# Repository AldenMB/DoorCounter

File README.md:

# DoorCounter
A IR beam detector for counting when people enter or exit a room, running on a Raspberry Pi Pico.

The DS1302 driver is from [Omar Benhamid](https://github.com/omarbenhamid/micropython-ds1302-rtc). Thanks Omar!

The rotary encoder driver is from [Mike Teachman](https://github.com/miketeachman/micropython-rotary). Thanks Mike!

The circuit board will be held in using 5/16 inch 2-28 pan-head screws. The heads have a diameter of 5/32 inches = 4 mm, The threaded portion has an exterior diameter of 3/32in = 2.3mm, and an inner diameter of about 1/16in = 1.6mm. They measure 3/8 inch in length, counting the head.

## Prototype error
Caution: in my first batch of boards I made an error in the schematic. Of course I take full responsibility, but I feel some blame shoudl also be shared by whoever decided to give one pin of the SD card the designation `DI` and another one the designation `D1`.

The error has already been fixed on the schematic, and it's easy enough to fix. Just break the trace going from `GP3` to the SD card, and instead run a wire to one side of `R3`. Like this:

Of course, if you don't use the SD card then this makes no difference. It is still pulled up to the `3V3` line with a 10k resistor.

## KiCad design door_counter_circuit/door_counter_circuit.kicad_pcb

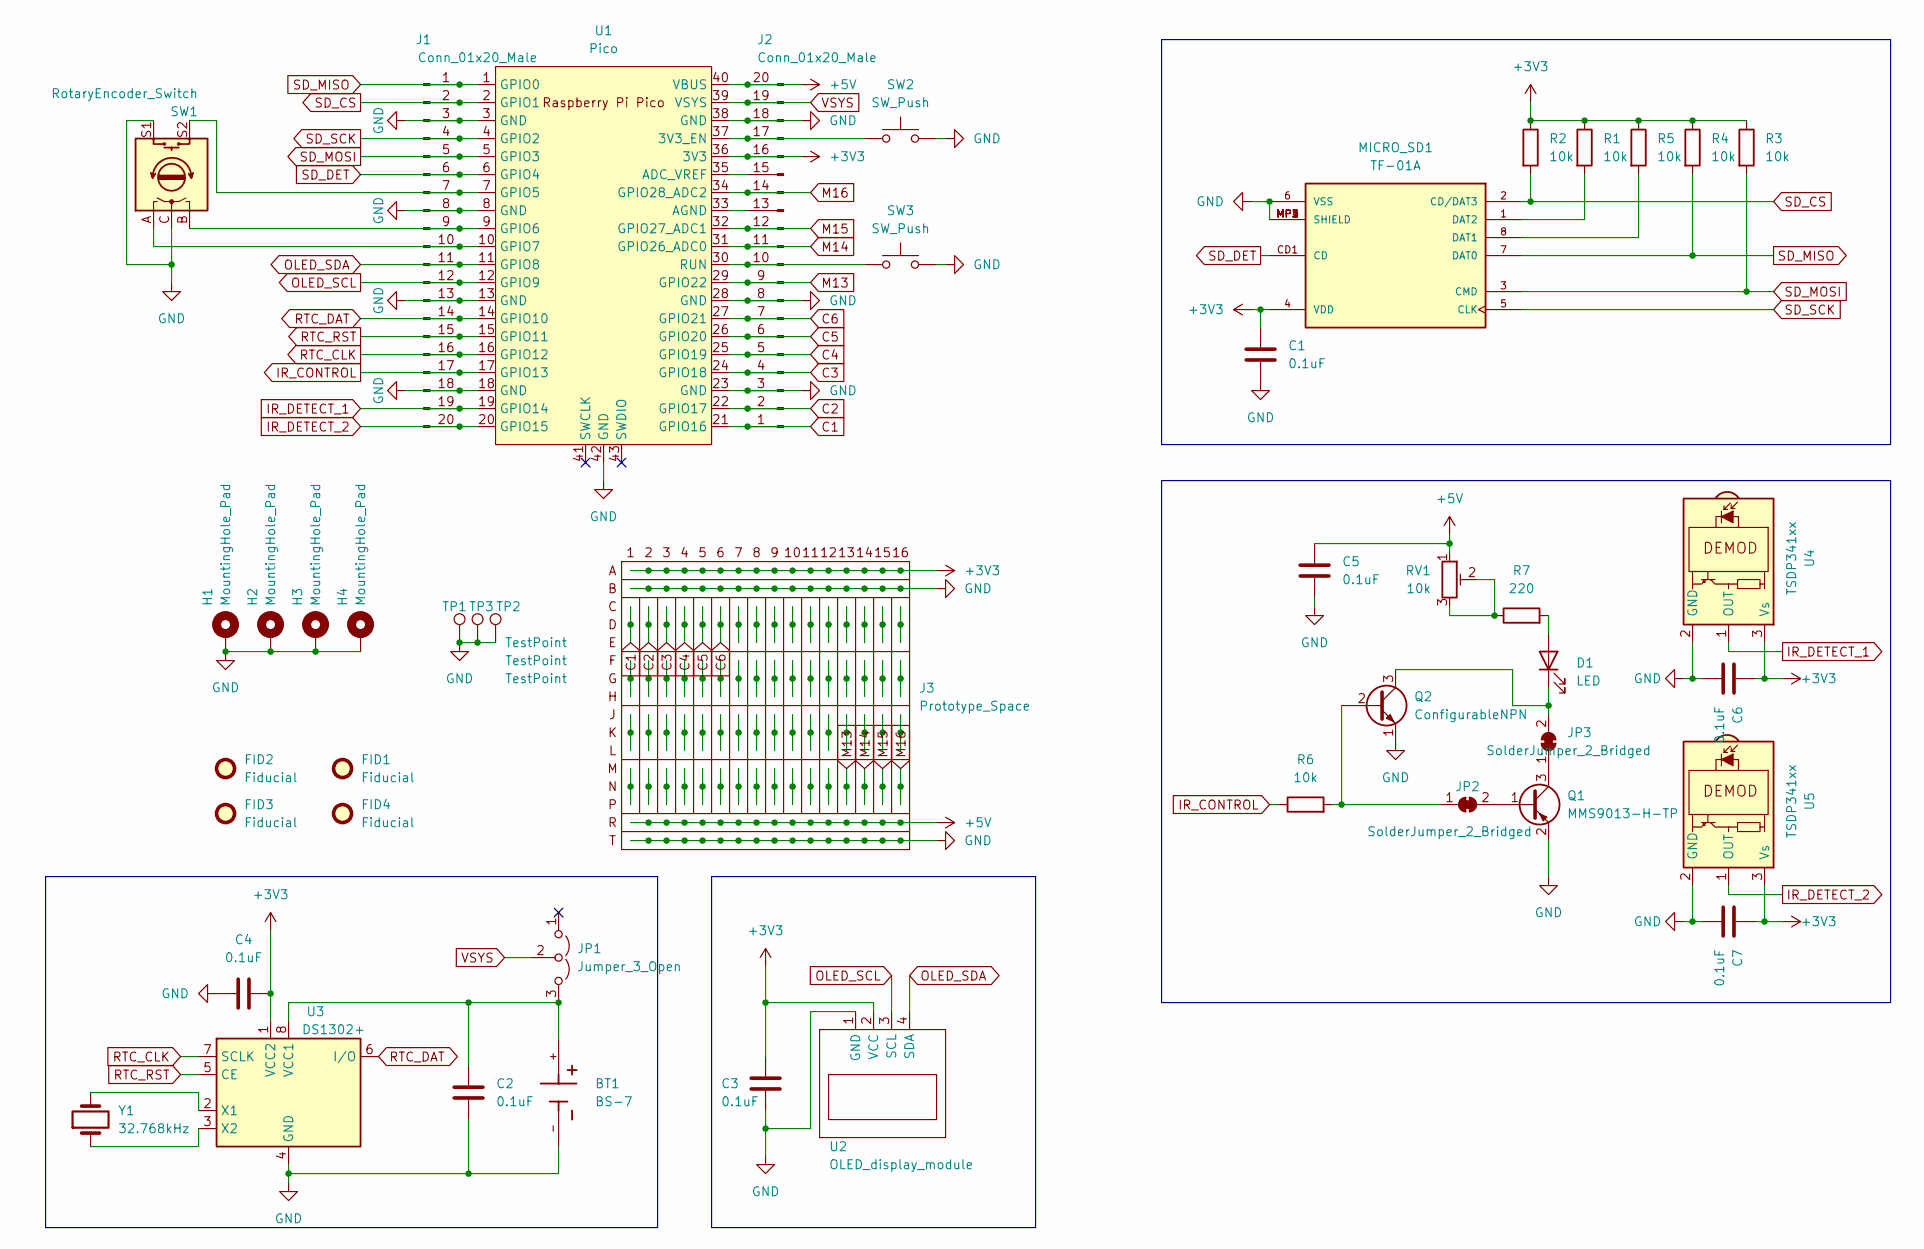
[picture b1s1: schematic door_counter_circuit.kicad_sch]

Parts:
BT1: BS-7; BAT_BS-7; PARTREV H
C1, C2, C3, C4, C5, C6, C7: 0.1uF; C_0402_1005Metric; LCSC C1525
D1: LED; LED_D3.0mm_Horizontal_O1.27mm_Z6.0mm
FID1, FID2, FID3, FID4: Fiducial; Fiducial_1mm_Mask2mm
H1, H2, H3, H4: MountingHole_Pad; MountingHole_2.5mm_Pad_Via
J1, J2: Conn_01x20_Male; PinHeader_1x20_P2.54mm_Vertical
J3: Prototype_Space; Prototype Space
JP1: Jumper_3_Open; PinHeader_1x03_P2.54mm_Vertical
JP2, JP3: SolderJumper_2_Bridged; SolderJumper-2_P1.3mm_Bridged_RoundedPad1.0x1.5mm
MICRO_SD1: TF-01A; LCSC C91145
Q1: MMS9013-H-TP; SOT-23; LCSC C90160
Q2: ConfigurableNPN; TO-92-configurable
R1, R2, R3, R4, R5, R6: 10k; R_0603_1608Metric; LCSC C25804
R7: 220; R_0805_2012Metric; LCSC C17557
RV1: 10k; Potentiometer_Bourns_3296W_Vertical
SW1: RotaryEncoder_Switch; RotaryEncoder_Alps_EC11E-Switch_Vertical_H20mm
SW2, SW3: SW_Push; SW_PUSH_6mm_H4.3mm
TP1, TP2, TP3: TestPoint; TestPoint_Pad_4.0x4.0mm
U1: Pico; RPi_Pico_SMD_TH
U2: OLED_display_module; SSD1306
U3: DS1302+; DIP-8_W7.62mm
U4, U5: TSDP341xx; Vishay_MOLD-3Pin
Y1: 32.768kHz; Crystal_C26-LF_D2.1mm_L6.5mm_Horizontal

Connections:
+3V3: C1.1, C3.1, C4.2, C6.1, C7.1, J2.16, J3.1A, J3.2A, J3.3A, J3.4A, J3.5A, J3.6A, J3.7A, J3.8A, J3.9A, J3.10A, J3.11A, J3.12A, J3.13A, J3.14A, J3.15A, J3.16A, MICRO_SD1.4 (VDD), R1.1, R2.1, R3.1, R4.1, R5.1, U1.36 (3V3), U2.2 (VCC), U3.1 (VCC2), U4.3 (Vs), U5.3 (Vs)
+5V: C5.1, J2.20, J3.1R, J3.2R, J3.3R, J3.4R, J3.5R, J3.6R, J3.7R, J3.8R, J3.9R, J3.10R, J3.11R, J3.12R, J3.13R, J3.14R, J3.15R, J3.16R, RV1.1, U1.40 (VBUS)
C1: J2.1, J3.1C, J3.1D, J3.1E, U1.21 (GPIO16)
C2: J2.2, J3.2C, J3.2D, J3.2E, U1.22 (GPIO17)
C3: J2.4, J3.3C, J3.3D, J3.3E, U1.24 (GPIO18)
C4: J2.5, J3.4C, J3.4D, J3.4E, U1.25 (GPIO19)
C5: J2.6, J3.5C, J3.5D, J3.5E, U1.26 (GPIO20)
C6: J2.7, J3.6C, J3.6D, J3.6E, U1.27 (GPIO21)
GND: BT1.-, C1.2, C2.2, C3.2, C4.1, C5.2, C6.2, C7.2, H1.1, H2.1, H3.1, H4.1, J1.3, J1.8, J1.13, J1.18, J2.3, J2.8, J2.18, J3.1B, J3.1T, J3.2B, J3.2T, J3.3B, J3.3T, J3.4B, J3.4T, J3.5B, J3.5T, J3.6B, J3.6T, J3.7B, J3.7T, J3.8B, J3.8T, J3.9B, J3.9T, J3.10B, J3.10T, J3.11B, J3.11T, J3.12B, J3.12T, J3.13B, J3.13T, J3.14B, J3.14T, J3.15B, J3.15T, J3.16B, J3.16T, MICRO_SD1.6 (VSS), MICRO_SD1.MP1 (SHIELD), MICRO_SD1.MP2 (SHIELD), MICRO_SD1.MP3 (SHIELD), MICRO_SD1.MP4 (SHIELD), Q1.2 (E), Q2.1 (E), Q2.4 (emitter_duplicate), SW1.C, SW1.S1, SW2.2, SW3.2, TP1.1, TP2.1, TP3.1, U1.3 (GND), U1.8 (GND), U1.13 (GND), U1.18 (GND), U1.23 (GND), U1.28 (GND), U1.38 (GND), U1.42 (GND), U2.1 (GND), U3.4 (GND), U4.2 (GND), U5.2 (GND)
IR_CONTROL: J1.17, R6.1, U1.17 (GPIO13)
IR_DETECT_1: J1.19, U1.19 (GPIO14), U4.1 (OUT)
IR_DETECT_2: J1.20, U1.20 (GPIO15), U5.1 (OUT)
M13: J2.9, J3.13M, J3.13N, J3.13P, U1.29 (GPIO22)
M14: J2.11, J3.14M, J3.14N, J3.14P, U1.31 (GPIO26_ADC0)
M15: J2.12, J3.15M, J3.15N, J3.15P, U1.32 (GPIO27_ADC1)
M16: J2.14, J3.16M, J3.16N, J3.16P, U1.34 (GPIO28_ADC2)
unnamed: BT1.+, C2.1, JP1.3 (B), U3.8 (VCC1)
unnamed: D1.1 (K), JP3.2 (B), Q2.3 (C), Q2.5 (collector_duplicate)
unnamed: D1.2 (A), R7.2
unnamed: J1.7, SW1.S2, U1.7 (GPIO5)
unnamed: J1.9, SW1.B, U1.9 (GPIO6)
unnamed: J1.10, SW1.A, U1.10 (GPIO7)
unnamed: J2.10, SW3.1, U1.30 (RUN)
unnamed: J2.13, U1.33 (AGND)
unnamed: J2.15, U1.35 (ADC_VREF)
unnamed: J2.17, SW2.1, U1.37 (3V3_EN)
unnamed: J3.1F, J3.1G, J3.1H
unnamed: J3.1J, J3.1K, J3.1L
unnamed: J3.1M, J3.1N, J3.1P
unnamed: J3.2F, J3.2G, J3.2H
unnamed: J3.2J, J3.2K, J3.2L
unnamed: J3.2M, J3.2N, J3.2P
unnamed: J3.3F, J3.3G, J3.3H
unnamed: J3.3J, J3.3K, J3.3L
unnamed: J3.3M, J3.3N, J3.3P
unnamed: J3.4F, J3.4G, J3.4H
unnamed: J3.4J, J3.4K, J3.4L
unnamed: J3.4M, J3.4N, J3.4P
unnamed: J3.5F, J3.5G, J3.5H
unnamed: J3.5J, J3.5K, J3.5L
unnamed: J3.5M, J3.5N, J3.5P
unnamed: J3.6F, J3.6G, J3.6H
unnamed: J3.6J, J3.6K, J3.6L
unnamed: J3.6M, J3.6N, J3.6P
unnamed: J3.7C, J3.7D, J3.7E
unnamed: J3.7F, J3.7G, J3.7H
unnamed: J3.7J, J3.7K, J3.7L
unnamed: J3.7M, J3.7N, J3.7P
unnamed: J3.8C, J3.8D, J3.8E
unnamed: J3.8F, J3.8G, J3.8H
unnamed: J3.8J, J3.8K, J3.8L
unnamed: J3.8M, J3.8N, J3.8P
unnamed: J3.9C, J3.9D, J3.9E
unnamed: J3.9F, J3.9G, J3.9H
unnamed: J3.9J, J3.9K, J3.9L
unnamed: J3.9M, J3.9N, J3.9P
unnamed: J3.10C, J3.10D, J3.10E
unnamed: J3.10F, J3.10G, J3.10H
unnamed: J3.10J, J3.10K, J3.10L
unnamed: J3.10M, J3.10N, J3.10P
unnamed: J3.11C, J3.11D, J3.11E
unnamed: J3.11F, J3.11G, J3.11H
unnamed: J3.11J, J3.11K, J3.11L
unnamed: J3.11M, J3.11N, J3.11P
unnamed: J3.12C, J3.12D, J3.12E
unnamed: J3.12F, J3.12G, J3.12H
unnamed: J3.12J, J3.12K, J3.12L
unnamed: J3.12M, J3.12N, J3.12P
unnamed: J3.13C, J3.13D, J3.13E
unnamed: J3.13F, J3.13G, J3.13H
unnamed: J3.13J, J3.13K, J3.13L
unnamed: J3.14C, J3.14D, J3.14E
unnamed: J3.14F, J3.14G, J3.14H
unnamed: J3.14J, J3.14K, J3.14L
unnamed: J3.15C, J3.15D, J3.15E
unnamed: J3.15F, J3.15G, J3.15H
unnamed: J3.15J, J3.15K, J3.15L
unnamed: J3.16C, J3.16D, J3.16E
unnamed: J3.16F, J3.16G, J3.16H
unnamed: J3.16J, J3.16K, J3.16L
unnamed: JP2.1 (A), Q2.2 (B), R6.2
unnamed: JP2.2 (B), Q1.1 (B)
unnamed: JP3.1 (A), Q1.3 (C)
unnamed: MICRO_SD1.1 (DAT2), R1.2
unnamed: MICRO_SD1.8 (DAT1), R5.2
unnamed: R7.1, RV1.2, RV1.3
unnamed: U3.2 (X1), Y1.2
unnamed: U3.3 (X2), Y1.1
OLED_SCL: J1.12, U1.12 (GPIO9), U2.3 (SCL)
OLED_SDA: J1.11, U1.11 (GPIO8), U2.4 (SDA)
RTC_CLK: J1.16, U1.16 (GPIO12), U3.7 (SCLK)
RTC_DAT: J1.14, U1.14 (GPIO10), U3.6 (I/O)
RTC_RST: J1.15, U1.15 (GPIO11), U3.5 (CE)
SD_CS: J1.2, MICRO_SD1.2 (CD/DAT3), R2.2, U1.2 (GPIO1)
SD_DET: J1.6, MICRO_SD1.CD1 (CD), U1.6 (GPIO4)
SD_MISO: J1.1, MICRO_SD1.7 (DAT0), R4.2, U1.1 (GPIO0)
SD_MOSI: J1.5, MICRO_SD1.3 (CMD), R3.2, U1.5 (GPIO3)
SD_SCK: J1.4, MICRO_SD1.5 (CLK), U1.4 (GPIO2)
VSYS: J2.19, JP1.2 (C), U1.39 (VSYS)

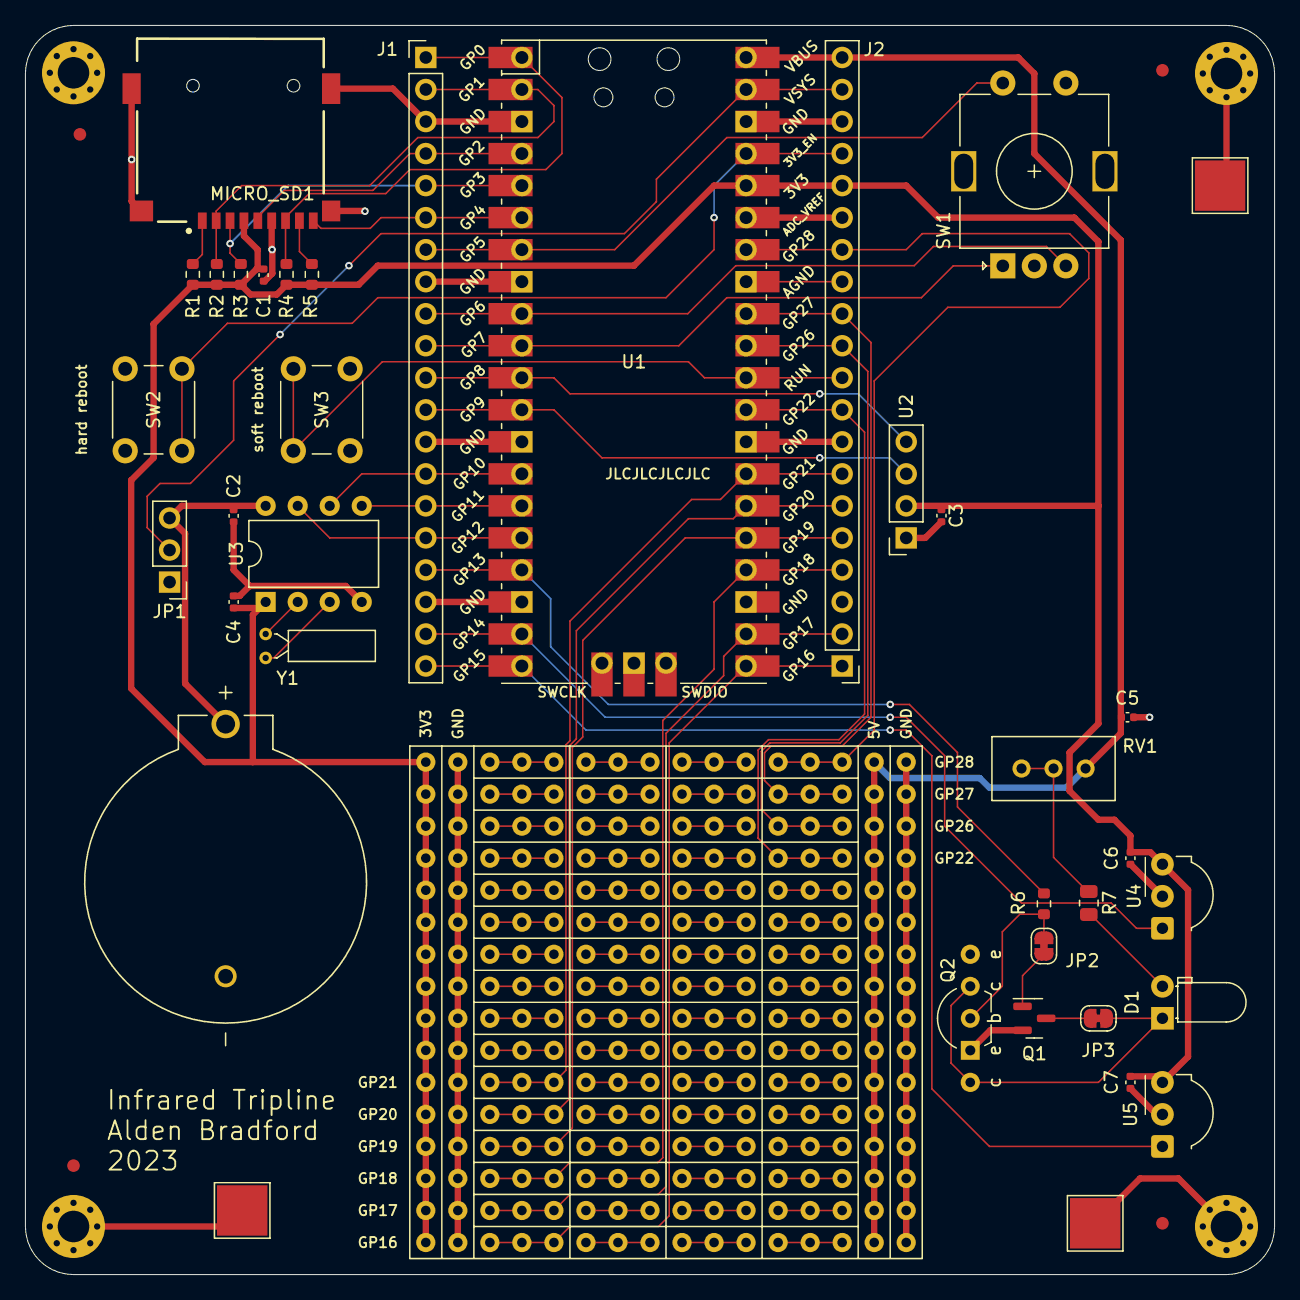
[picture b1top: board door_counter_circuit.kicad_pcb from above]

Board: 4 copper layers, 99.1 x 99.1 mm, 46 parts (0 on the bottom side), 99 nets.

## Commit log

2023-01-13 use a simpler protocol for faster detection
2023-01-13 read from sensors in PIO loop
2023-01-15 begin circuit schematic
2023-01-15 RTC driver
2023-01-15 all hardware connected
2023-01-16 circuit board drafted
2023-01-30 include measurements for screws
2023-01-30 include a configurable transistor footprint
2023-01-30 manufacturing outputs
2023-02-14 match pinout of PCB
2023-02-14 fix to SD circuit
